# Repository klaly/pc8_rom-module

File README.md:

# pc8_rom-module
This is a ROM-Pack PCB for a TA alphatronic PC8 computer

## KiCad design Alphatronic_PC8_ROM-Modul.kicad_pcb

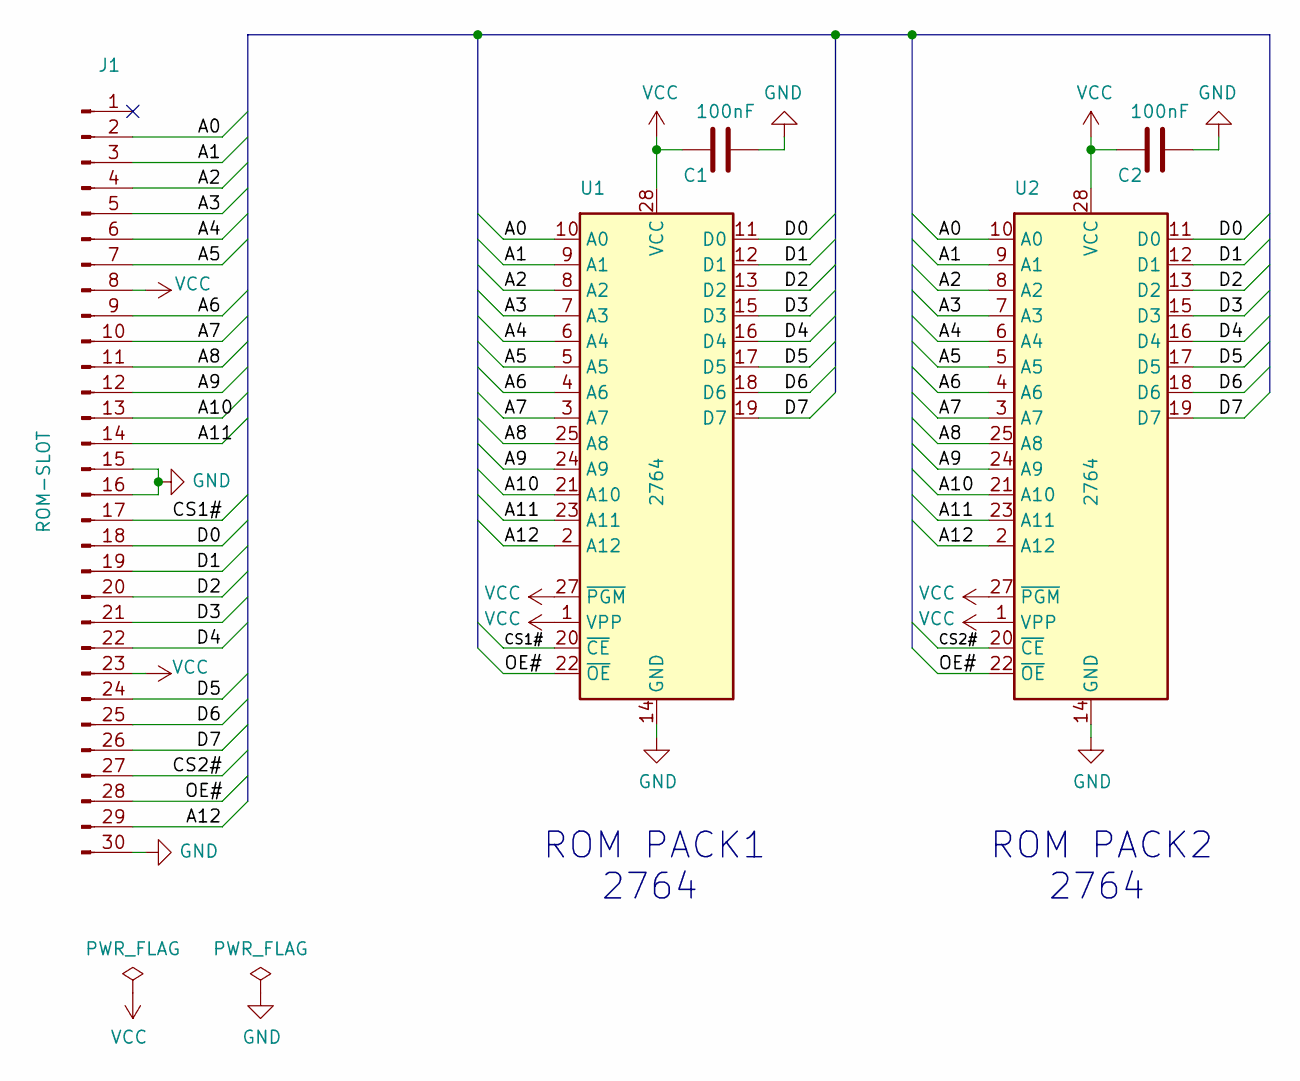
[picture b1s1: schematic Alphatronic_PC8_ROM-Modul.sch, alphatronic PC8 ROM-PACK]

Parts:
C1, C2: 100nF; C_Disc_D5.1mm_W3.2mm_P5.00mm
J1: ROM-SLOT; PC8_ROM_SLOT
U1, U2: 2764; DIP-28_W15.24mm

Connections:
/A0: J1.2, U1.10 (A0), U2.10 (A0)
/A1: J1.3, U1.9 (A1), U2.9 (A1)
/A2: J1.4, U1.8 (A2), U2.8 (A2)
/A3: J1.5, U1.7 (A3), U2.7 (A3)
/A4: J1.6, U1.6 (A4), U2.6 (A4)
/A5: J1.7, U1.5 (A5), U2.5 (A5)
/A6: J1.9, U1.4 (A6), U2.4 (A6)
/A7: J1.10, U1.3 (A7), U2.3 (A7)
/A8: J1.11, U1.25 (A8), U2.25 (A8)
/A9: J1.12, U1.24 (A9), U2.24 (A9)
/A10: J1.13, U1.21 (A10), U2.21 (A10)
/A11: J1.14, U1.23 (A11), U2.23 (A11)
/A12: J1.29, U1.2 (A12), U2.2 (A12)
/CS1#: J1.17, U1.20 (~CE)
/CS2#: J1.27, U2.20 (~CE)
/D0: J1.18, U1.11 (D0), U2.11 (D0)
/D1: J1.19, U1.12 (D1), U2.12 (D1)
/D2: J1.20, U1.13 (D2), U2.13 (D2)
/D3: J1.21, U1.15 (D3), U2.15 (D3)
/D4: J1.22, U1.16 (D4), U2.16 (D4)
/D5: J1.24, U1.17 (D5), U2.17 (D5)
/D6: J1.25, U1.18 (D6), U2.18 (D6)
/D7: J1.26, U1.19 (D7), U2.19 (D7)
/OE#: J1.28, U1.22 (~OE), U2.22 (~OE)
GND: C1.1, C2.1, J1.15, J1.16, J1.30, U1.14 (GND), U2.14 (GND)
VCC: C1.2, C2.2, J1.8, J1.23, U1.1 (VPP), U1.27 (~PGM), U1.28 (VCC), U2.1 (VPP), U2.27 (~PGM), U2.28 (VCC)

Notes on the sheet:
ROM PACK1 2764
ROM PACK2 2764

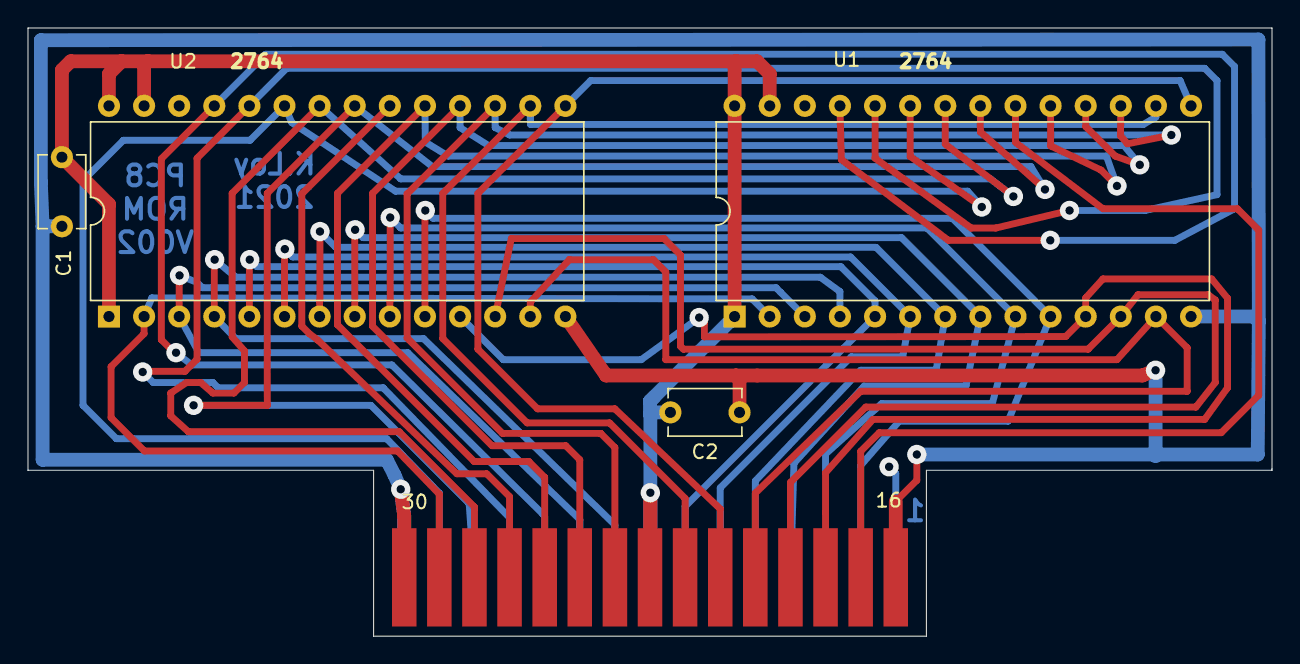
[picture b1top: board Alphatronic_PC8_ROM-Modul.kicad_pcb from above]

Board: 2 copper layers, 90.0 x 44.0 mm, 5 parts (0 on the bottom side), 26 nets.

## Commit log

2021-01-24 upload files Version 2
